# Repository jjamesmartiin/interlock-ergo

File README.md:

# Interlock Ergo

> **Disclaimer:** This project (firmware, PCB generation scripts, CAD models, and documentation) is an experimental keyboard design developed and maintained with AI assistance. Always verify schematics, board dimensions, gerber files, and dry-fit clearances before ordering physical fabrication or soldering components.

A wireless 68-key split ergonomic keyboard that **docks into one rigid keyboard**.
The two halves carry matching dovetail tabs and flush N52 magnets: lower one onto
the other and the joint closes, lift one and they separate. Both halves talk to a
USB dongle over low-power Bluetooth LE, so the host sees one ordinary USB HID
keyboard with no pairing and no drivers.

Two complete hardware variants are published, each with its own PCB and plate:

| | **Choc v1** | **Cherry MX** |
|---|---|---|
| Pitch | 18.0 × 17.0 mm | 19.05 × 19.05 mm |
| Plate | 1.2 mm | 1.5 mm |
| Case height | 14.2 mm | 16.0 mm |
| Case, docked | 350.2 × 137.6 mm | 367.5 × 147.8 mm |

---

## What makes it different

1. **It becomes one keyboard.** The left half carries two dovetail tabs on its
   seam face; the right half has the matching blind sockets. Four 6×3 mm N52
   magnets, flush with the seam faces, hold the joint closed. The undercut profile
   carries the load in tension and shear, so the seam behaves as one panel rather
   than two cases pushed together.
2. **A real USB keyboard, wirelessly.** A XIAO nRF52840 dongle is the ZMK split
   central and enumerates as a plain USB HID device. The halves reach it over
   Bluetooth LE at 2.4 GHz and bond with it once; the *host* never sees a
   Bluetooth device, so there is no pairing, no driver, and nothing to re-pair
   when you move between machines. It works in BIOS/UEFI and on laptops where
   Bluetooth is locked down by policy. Bluetooth profiles remain available
   (`&out OUT_BLE`) for phones and tablets.
3. **68 keys, all 1u.** No stabilisers, no wide keys, no non-standard keycap sizes
   to hunt for. ANSI row stagger (0 / 0.5 / 0.75 / 1.25 / 0.25 u) puts every letter
   column at the same offset it has on a GH60, so touch-typing transfers unchanged.
   There is no function column: 6 columns on the left and 8 on the right match a DZ60
   split down the middle (between 5 and 6), with a true inverted-T arrow cluster on
   the bottom right.
   The PCB, plate and case share one band stack, so the silhouette steps with the
   stagger and hugs the keys instead of being a rectangle with dead copper down one
   side of every row. The seam face stays a straight plane - it is the joint.

The diagram above is generated from the same constants the CAD and the PCB use
(`node docs/generate_layout.js`), so it cannot drift away from the hardware. Two
consequences of the straight seam that are worth knowing before you build:

- The row stagger needs 22.5 mm of horizontal shear. With a straight seam that
  shear ends up as dead case width on each half's seam edge, so the **centre gap
  between `5` and `6` is 69.1 mm (3.8 u)**, not the ~1.5 u of a normal staggered
  board. It is the same on every row. That is the price of a straight seam plane;
  a stepped seam would close it and is on the roadmap.
- `6`, `Y`, `H` and `N` all land on the right half (red column in the diagram),
  which is the usual convention for 6-column splits and matches ANSI.

---

## The parts

| | |
|---|---|
|  |  |
| Left half: seam face with the two dovetail tabs, USB-C window with its overmold relief, and the open controller bay | Right half: blind dovetail sockets and flush magnet pockets in the seam wall |
|  |  |
| Underside: four M2 bosses with the PCB mounts, cell recess in the controller bay | Plates: 14.0 mm switch apertures, stepped outline |
|  | |

Every STL in `cad/dist/` is gated by `tests/test_models.js`, which fails the
build if a part is more than one shell, is not watertight, or its dimensions
disagree with the stackup in `cad/interlock_params.scad`.

---

## Layout

```
[Esc  ] [1    ] [2    ] [3    ] [4    ] [5    ]  ‖ [6    ] [7    ] [8    ] [9    ] [0    ] [-    ] [=    ] [Bksp ]
   [Tab  ] [Q    ] [W    ] [E    ] [R    ] [T    ]  ‖ [Y    ] [U    ] [I    ] [O    ] [P    ] [[    ] []    ] [\    ]
     [Caps ] [A    ] [S    ] [D    ] [F    ] [G    ]  ‖ [H    ] [J    ] [K    ] [L    ] [;    ] ['    ] [Enter]
        [Shift] [Z    ] [X    ] [C    ] [V    ] [B    ]  ‖ [N    ] [M    ] [,    ] [.    ] [/    ] [Up   ] [Shift] [Del  ]
  [Ctrl ] [Win  ] [Alt  ] [Space] [Fn1  ]  ‖ [Space] [Alt  ] [Fn1  ] [Win  ] [Ctrl ] [Left ] [Down ] [Right]
```

Printed by `node docs/generate_layout.js` straight out of the keymap, with each
row indented by its ANSI stagger. 68 keys: 29 left + 39 right, in a 5 × 14 matrix.
`docs/kle_layout.json` is the same layout as a Keyboard-Layout-Editor file, and
`docs/matrix_and_pinout.md` has the electrical side. There is no function column
and no rotary encoder: both went when the layout was pulled back onto GH60's columns,
which is also why the left half is 29 keys and not 34.

---

## Repository

```
├── .github/workflows/build-zmk.yml   # firmware build + matrix tests + PCB DRC gate
├── cad/
│   ├── interlock_params.scad         # stackup, tolerances, joint and magnet geometry
│   ├── interlock_case.scad           # the case, shared by both switch standards
│   ├── interlock_case_{choc,mx}.scad # variant wrappers
│   ├── interlock_plate.scad          # switch plate, shared by both standards
│   ├── interlock_plate_{choc,mx}.scad
│   ├── dongle_case.scad              # XIAO BLE tray + friction-fit lid
│   ├── build_models.js               # headless STL build -> cad/dist/
│   ├── render_preview.js             # headless STL -> docs/images/*.png
│   └── dist/                         # printable STLs (generated, not committed)
├── config/boards/shields/interlock_ergo/
│   ├── Kconfig.shield, Kconfig.defconfig
│   ├── interlock_ergo.dtsi           # 68-key matrix transform
│   ├── interlock_ergo_{left,right,dongle}.overlay
│   ├── interlock_ergo_{left,right,dongle}.conf
│   └── interlock_ergo.keymap         # QWERTY, Nav/Fn, Media/BLE layers
├── docs/
│   ├── architecture.md               # design rationale and the dongle topology
│   ├── assembly.md                   # build order, torque, magnet polarity, flash steps
│   ├── bom.md                        # parts with vendor links
│   ├── matrix_and_pinout.md          # GPIO map and power tree
│   ├── part-dimensions.md            # every dimension the CAD rests on, with sources
│   ├── generate_layout.js            # draws docs/images/layout.svg from the real numbers
│   └── production-readiness-audit.md # adversarial review of the current tree
├── pcb/generate_pcb.js               # KiCad board generator + router + DRC gate
├── pcb/generate_schematic.js         # .kicad_sch from the verified board, with ERC
├── pcb/*.kicad_pcb                   # four boards: {left,right} x {choc,mx}
├── pcb/dist/                         # gerbers/BOM/CPL/schematic, only for DRC-clean boards
└── tests/
    ├── test_matrix.js                # firmware matrix, Kconfig, stagger agreement
    ├── test_models.js                # mesh watertightness + dimension gate
    ├── test_alignment.js             # PCB footprints vs plate apertures vs case rebate
    └── test_fab_rules.js             # process limits + order quantity per design
```

---

## Build and verify

```bash
node tests/test_matrix.js     # firmware matrix, shield config, CAD/PCB stagger agreement
node tests/test_models.js     # every STL is one watertight shell of the right size
node tests/test_alignment.js  # PCB footprints vs plate apertures vs case rebate, sampled in the meshes
node tests/test_fab_rules.js   # JLCPCB process limits and the order quantity per design
node cad/build_models.js      # rebuild all STLs
node cad/render_preview.js    # rebuild the README renders
node docs/generate_layout.js  # rebuild the layout diagram
node pcb/generate_pcb.js      # regenerate boards; DRC-clean boards emit fab files
node pcb/generate_schematic.js # regenerate the .kicad_sch files and their ERC/netlist gate
```

`pcb/generate_pcb.js` refuses to emit gerbers, BOM or CPL for any board that has
DRC violations or unconnected pads - **at any severity**, warnings included - and
withdraws previously published ones.
**If a gerber zip is missing from `pcb/dist/`, that board is not orderable** - fix
the routing, do not hand-build a zip from `pcb/*.kicad_pcb`.

Fabrication output is reproducible: KiCad's creation timestamps are pinned, so two
runs from the same sources produce byte-identical gerbers and a "gerbers changed"
diff always means the copper changed.

All of the above run in CI, including the DRC gate.

---

## Bill of materials

Full sourcing with vendor links: [docs/bom.md](docs/bom.md).

| Item | Qty | Notes |
|---|---|---|
| nice!nano v2 | 2 | one per half, castellated or socketed |
| Seeed XIAO nRF52840 (BLE) | 1 | USB dongle (central) |
| Kailh Choc v1 PG1350 **or** Cherry MX switches | 68 | pick one variant, not both |
| Kailh hotswap sockets | 68 | Choc `CPG135001S30` / MX `CPG151101S11`. The pin holes are unplated: **hotswap only**, switches cannot be soldered in directly |
| 1N4148W SOD-123 | 68 | one per key |
| MSK-12D19 slide switch | 2 | power, one per half |
| JST-PH 2.0 | 2 | cell connector |
| Protected LiPo pouch, LP402030 (4 × 20 × 30 mm cell) | 2 | ~200 mAh, **must** have a PCM — the PCM adds ~3.2 mm, so allow 34 mm overall |
| 6 × 3 mm N52 disc magnets | 4 | two per seam |
| M2 × 5 self-tapping screws | 8 | four per half |
| Plates | 1 pair | 3D printed, or 1.2 mm FR4 for Choc |

Battery reality check: the controller bay takes a 4.5 mm pack, and the documented
402030 is a **200 mAh** cell — not 250. With `CONFIG_ZMK_IDLE_SLEEP_TIMEOUT=900000`
that is roughly **1-2 weeks between charges**, not months. A bigger cell needs a
taller `standoff_h` in `cad/interlock_params.scad` and a re-print of both halves.

---

## Manufacturing

### PCBs

1. `node pcb/generate_pcb.js`. Only DRC-clean boards are written to `pcb/dist/`.
   `node pcb/generate_schematic.js` then emits the matching `.kicad_sch` and fails if
   its netlist disagrees with the board.
2. Order from JLCPCB: 2 layers, 1.6 mm, 1 oz copper, ENIG recommended for the
   hotswap pads, at the quantity in item 3 (5 pcs crosses the 650 cm² order-area
   threshold and adds a large-order surcharge).
3. **Quantity per design, not one number for everything.** The order-area budget is
   650 cm² and the boards are different sizes, so the right quantity differs:
   left Choc 3 pcs, right Choc 2, left MX 2, right MX 2. `node tests/test_fab_rules.js`
   prints the numbers for however you regenerate the boards - re-check them on the
   live JLCPCB quote, since the thresholds and fees change.
4. `bom_*.csv` / `cpl_*.csv` are only emitted for diodes, and the gerber zip
   carries the `B.Paste` stencil layer for them. Order them placed, or hand-solder
   them with everything else (sockets, headers, JST, slide switch) - hand-soldering
   is cheaper than JLCPCB's per-order PCBA fees at this volume.
5. Order both design variants only if you intend to build both; each half is a
   separate board because the halves are 29 and 39 keys and cannot be reversible.

### Printing

- PETG, 0.16 mm layers, 4 perimeters, 20% gyroid.
- Cases: print with the floor down. The seam tabs and the bay are vertical walls,
  so nothing needs support; only the two magnet pockets bridge, over 3.2 mm.
- Plates: 1.2 mm (Choc) / 1.5 mm (MX) exactly. Do not scale.
- Dongle: `dongle_case_base.stl` + `dongle_case_lid.stl`.
- Bed size: the left case is 160 × 138 mm, the right 193 × 138 mm (203 for MX), so a 220 × 220
  bed fits either half and a 256 × 256 bed fits both.

### Assembly

See [docs/assembly.md](docs/assembly.md). The order matters: solder the sockets
and diodes on the **bottom** of the PCB, screw the PCB to the four bosses, then
drop the plate in **last** - the switches hold the plate down.

---

## Firmware

CI builds all three shields. Download the artifact zip, then flash:

| Board | File |
|---|---|
| left half (nice!nano v2) | `interlock_ergo_left-nice_nano_v2-zmk.uf2` |
| right half (nice!nano v2) | `interlock_ergo_right-nice_nano_v2-zmk.uf2` |
| dongle (XIAO BLE) | `interlock_ergo_dongle-seeeduino_xiao_ble-zmk.uf2` |

CI also builds the dongle shield for `nice_nano_v2` and `nrf52840dongle_nrf52840`.
Those are firmware-only targets: the printed dongle case fits the XIAO, and the
Nordic USB-A dongle is a stick with no enclosure.

Double-tap reset to enter the UF2 bootloader and copy the file across. The dongle
bonds with both halves on first boot.

If the halves stop connecting after a reflash or a controller swap, flash
`settings_reset` on both halves and re-pair - it is built by the same workflow.

Local builds with Nix are available from `flake.nix`
(`nix build .#firmware-left`, `.#firmware-right`, `.#firmware-dongle`, `.#cad`, `.#pcb`,
or just `nix build` for the full release package).

All three shields are built and checked in CI. Two firmware details are pinned
rather than left to chance:

- `config/west.yml` pins ZMK **v0.2** (Zephyr 3.5).
- `flake.nix` pins the ARM compiler to **GCC 13**. nixpkgs' current
  `gcc-arm-embedded` is GCC 15, which rejects ZMK v0.2's `int` → `void *`
  `user_data` cast in `central_bas_proxy.c` as a hard error. Upstream only fixed
  that after v0.3.0 ([zmkfirmware/zmk#3105](https://github.com/zmkfirmware/zmk/pull/3105)).
  Move both pins together when you bump ZMK.

---

## Status

Every gate in this repository passes: the firmware matrix, the 3D-printed parts,
the plate/case/PCB alignment, the PCB DRC gate, and the fabrication-rule limits. All four boards route clean and
their JLCPCB gerber/BOM/CPL packages are in `pcb/dist/`.

What has *not* happened is a physical build. Nothing here has been printed,
soldered or typed on. Before ordering PCBs, print one half and dry-fit it - see
step 1 of [docs/assembly.md](docs/assembly.md).

Known limitations, in full: [docs/production-readiness-audit.md](docs/production-readiness-audit.md)
(69 mm docked centre gap, 200 mAh cell ceiling, no ESD/TVS protection).

Every mechanical dimension the CAD rests on, and where it came from:
[docs/part-dimensions.md](docs/part-dimensions.md).

## License

MIT. See [LICENSE](LICENSE).

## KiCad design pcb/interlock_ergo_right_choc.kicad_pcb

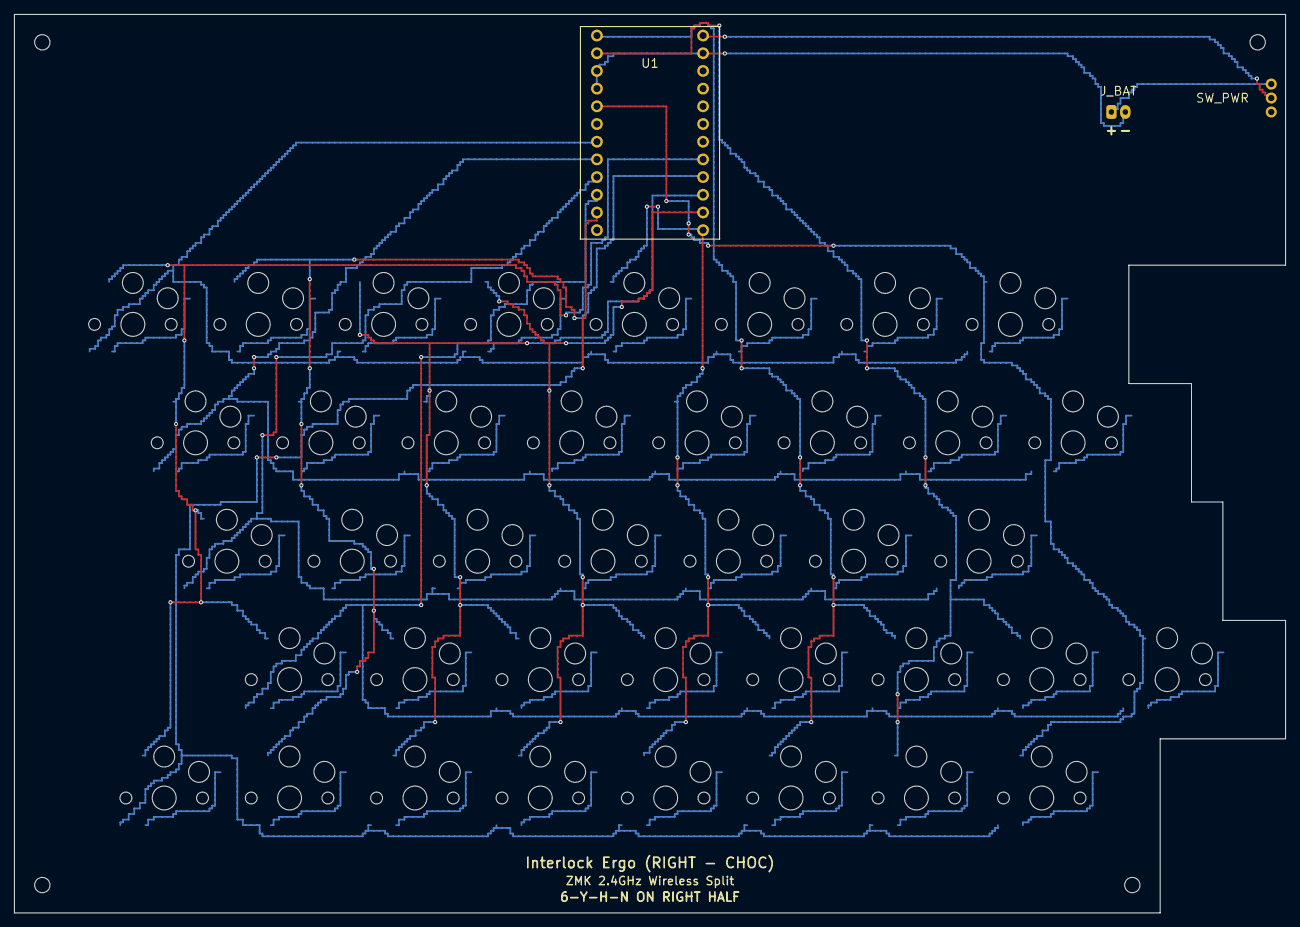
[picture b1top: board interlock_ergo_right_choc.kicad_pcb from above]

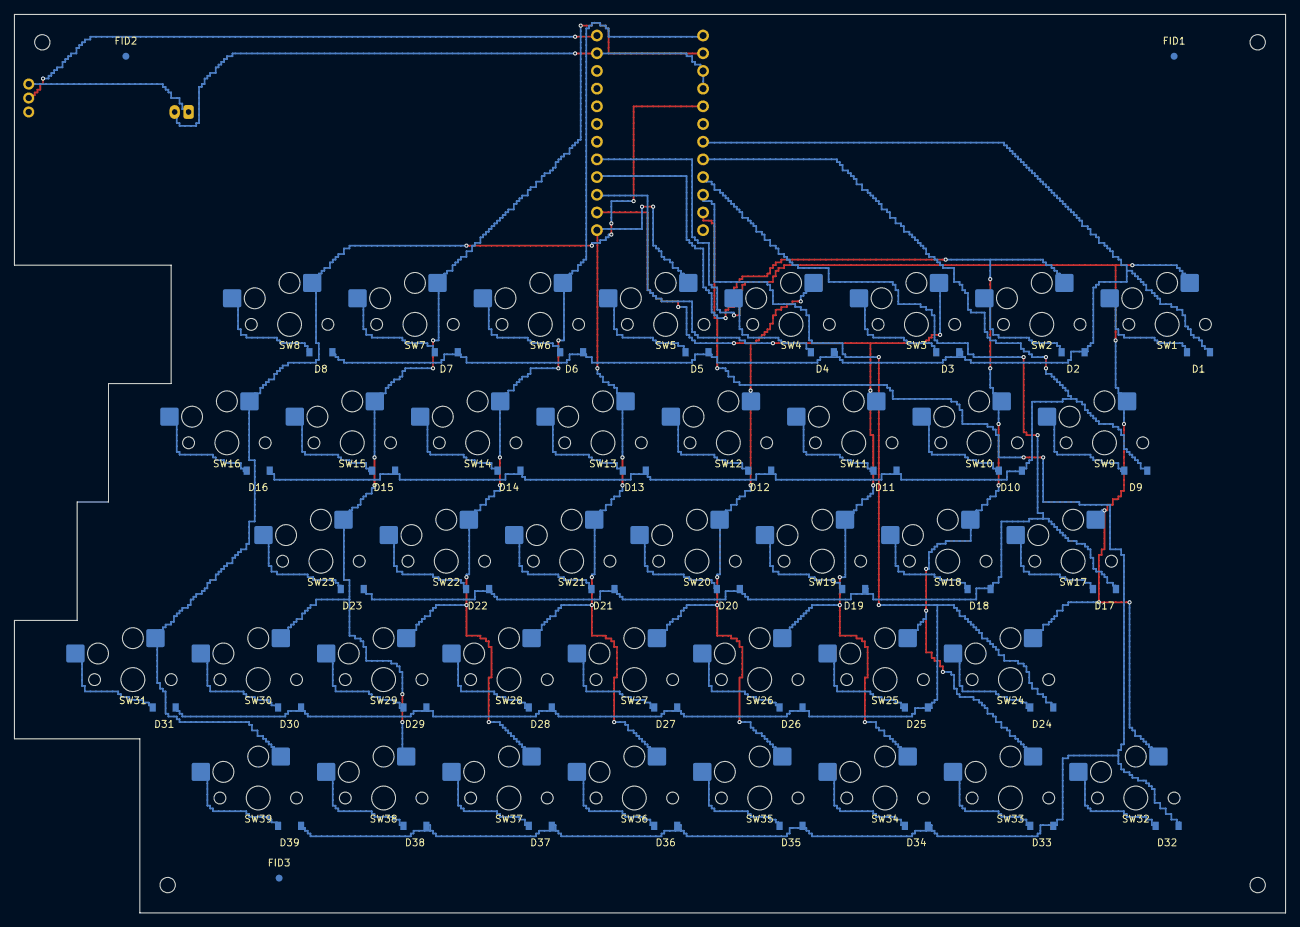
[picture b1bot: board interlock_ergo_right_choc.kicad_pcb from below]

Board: 2 copper layers, 182.5 x 129.0 mm, 84 parts (81 on the bottom side), 55 nets.

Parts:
D1, D2, D3, D4, D5, D6, D7, D8, D9, D10, D11, D12, D13, D14, D15, D16, D17, D18, D19, D20, D21, D22, D23, D24, D25, D26, D27, D28, D29, D30, D31, D32, D33, D34, D35, D36, D37, D38, D39: D_SOD-123
FID1, FID2, FID3: Fiducial_1mm_Mask2mm
J_BAT: JST_PH_S2B-PH-K_1x02
SW1, SW2, SW3, SW4, SW5, SW6, SW7, SW8, SW9, SW10, SW11, SW12, SW13, SW14, SW15, SW16, SW17, SW18, SW19, SW20, SW21, SW22, SW23, SW24, SW25, SW26, SW27, SW28, SW29, SW30, SW31, SW32, SW33, SW34, SW35, SW36, SW37, SW38, SW39: Kailh_Choc_V1_CPG135001S30
SW_PWR: SlideSwitch_MSK12D19
U1: NiceNano_v2_ProMicro

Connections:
BAT_PLUS: J_BAT.1, SW_PWR.1
COL6: SW1.1, SW9.1, SW17.1, SW24.1, SW32.1, U1.20
COL7: SW2.1, SW10.1, SW18.1, SW25.1, SW33.1, U1.21
COL8: SW3.1, SW11.1, SW19.1, SW26.1, SW34.1, U1.22
COL9: SW4.1, SW12.1, SW20.1, SW27.1, SW35.1, U1.23
COL10: SW5.1, SW13.1, SW21.1, SW28.1, SW36.1, U1.24
COL11: SW6.1, SW14.1, SW22.1, SW29.1, SW37.1, U1.1
COL12: SW7.1, SW15.1, SW23.1, SW30.1, SW38.1, U1.2
COL13: SW8.1, SW16.1, SW31.1, SW39.1, U1.5
GND: J_BAT.2, U1.3, U1.4, U1.14
RAW: SW_PWR.2, U1.13
ROW0: D1.1, D2.1, D3.1, D4.1, D5.1, D6.1, D7.1, D8.1, U1.7
ROW1: D9.1, D10.1, D11.1, D12.1, D13.1, D14.1, D15.1, D16.1, U1.8
ROW2: D17.1, D18.1, D19.1, D20.1, D21.1, D22.1, D23.1, U1.9
ROW3: D24.1, D25.1, D26.1, D27.1, D28.1, D29.1, D30.1, D31.1, U1.10
ROW4: D32.1, D33.1, D34.1, D35.1, D36.1, D37.1, D38.1, D39.1, U1.11
SW_D_R0_C0: D1.2, SW1.2
SW_D_R0_C1: D2.2, SW2.2
SW_D_R0_C2: D3.2, SW3.2
SW_D_R0_C3: D4.2, SW4.2
SW_D_R0_C4: D5.2, SW5.2
SW_D_R0_C5: D6.2, SW6.2
SW_D_R0_C6: D7.2, SW7.2
SW_D_R0_C7: D8.2, SW8.2
SW_D_R1_C0: D9.2, SW9.2
SW_D_R1_C1: D10.2, SW10.2
SW_D_R1_C2: D11.2, SW11.2
SW_D_R1_C3: D12.2, SW12.2
SW_D_R1_C4: D13.2, SW13.2
SW_D_R1_C5: D14.2, SW14.2
SW_D_R1_C6: D15.2, SW15.2
SW_D_R1_C7: D16.2, SW16.2
SW_D_R2_C0: D17.2, SW17.2
SW_D_R2_C1: D18.2, SW18.2
SW_D_R2_C2: D19.2, SW19.2
SW_D_R2_C3: D20.2, SW20.2
SW_D_R2_C4: D21.2, SW21.2
SW_D_R2_C5: D22.2, SW22.2
SW_D_R2_C6: D23.2, SW23.2
SW_D_R3_C0: D24.2, SW24.2
SW_D_R3_C1: D25.2, SW25.2
SW_D_R3_C2: D26.2, SW26.2
SW_D_R3_C3: D27.2, SW27.2
SW_D_R3_C4: D28.2, SW28.2
SW_D_R3_C5: D29.2, SW29.2
SW_D_R3_C6: D30.2, SW30.2
SW_D_R3_C7: D31.2, SW31.2
SW_D_R4_C0: D32.2, SW32.2
SW_D_R4_C1: D33.2, SW33.2
SW_D_R4_C2: D34.2, SW34.2
SW_D_R4_C3: D35.2, SW35.2
SW_D_R4_C4: D36.2, SW36.2
SW_D_R4_C5: D37.2, SW37.2
SW_D_R4_C6: D38.2, SW38.2
SW_D_R4_C7: D39.2, SW39.2

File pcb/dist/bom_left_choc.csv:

Comment,Designator,Footprint,LCSC Part #
Kailh Choc Hotswap Socket CPG135001S30,SW1,Kailh_Choc_V1_CPG135001S30,C5333465
1N4148W,D1,SOD-123,C81598
Kailh Choc Hotswap Socket CPG135001S30,SW2,Kailh_Choc_V1_CPG135001S30,C5333465
1N4148W,D2,SOD-123,C81598
Kailh Choc Hotswap Socket CPG135001S30,SW3,Kailh_Choc_V1_CPG135001S30,C5333465
1N4148W,D3,SOD-123,C81598
Kailh Choc Hotswap Socket CPG135001S30,SW4,Kailh_Choc_V1_CPG135001S30,C5333465
1N4148W,D4,SOD-123,C81598
Kailh Choc Hotswap Socket CPG135001S30,SW5,Kailh_Choc_V1_CPG135001S30,C5333465
1N4148W,D5,SOD-123,C81598
Kailh Choc Hotswap Socket CPG135001S30,SW6,Kailh_Choc_V1_CPG135001S30,C5333465
1N4148W,D6,SOD-123,C81598
Kailh Choc Hotswap Socket CPG135001S30,SW7,Kailh_Choc_V1_CPG135001S30,C5333465
1N4148W,D7,SOD-123,C81598
Kailh Choc Hotswap Socket CPG135001S30,SW8,Kailh_Choc_V1_CPG135001S30,C5333465
1N4148W,D8,SOD-123,C81598
Kailh Choc Hotswap Socket CPG135001S30,SW9,Kailh_Choc_V1_CPG135001S30,C5333465
1N4148W,D9,SOD-123,C81598
Kailh Choc Hotswap Socket CPG135001S30,SW10,Kailh_Choc_V1_CPG135001S30,C5333465
1N4148W,D10,SOD-123,C81598
Kailh Choc Hotswap Socket CPG135001S30,SW11,Kailh_Choc_V1_CPG135001S30,C5333465
1N4148W,D11,SOD-123,C81598
Kailh Choc Hotswap Socket CPG135001S30,SW12,Kailh_Choc_V1_CPG135001S30,C5333465
1N4148W,D12,SOD-123,C81598
Kailh Choc Hotswap Socket CPG135001S30,SW13,Kailh_Choc_V1_CPG135001S30,C5333465
1N4148W,D13,SOD-123,C81598
Kailh Choc Hotswap Socket CPG135001S30,SW14,Kailh_Choc_V1_CPG135001S30,C5333465
1N4148W,D14,SOD-123,C81598
Kailh Choc Hotswap Socket CPG135001S30,SW15,Kailh_Choc_V1_CPG135001S30,C5333465
1N4148W,D15,SOD-123,C81598
Kailh Choc Hotswap Socket CPG135001S30,SW16,Kailh_Choc_V1_CPG135001S30,C5333465
1N4148W,D16,SOD-123,C81598
Kailh Choc Hotswap Socket CPG135001S30,SW17,Kailh_Choc_V1_CPG135001S30,C5333465
1N4148W,D17,SOD-123,C81598
Kailh Choc Hotswap Socket CPG135001S30,SW18,Kailh_Choc_V1_CPG135001S30,C5333465
1N4148W,D18,SOD-123,C81598
Kailh Choc Hotswap Socket CPG135001S30,SW19,Kailh_Choc_V1_CPG135001S30,C5333465
1N4148W,D19,SOD-123,C81598
Kailh Choc Hotswap Socket CPG135001S30,SW20,Kailh_Choc_V1_CPG135001S30,C5333465
1N4148W,D20,SOD-123,C81598
Kailh Choc Hotswap Socket CPG135001S30,SW21,Kailh_Choc_V1_CPG135001S30,C5333465
1N4148W,D21,SOD-123,C81598
Kailh Choc Hotswap Socket CPG135001S30,SW22,Kailh_Choc_V1_CPG135001S30,C5333465
1N4148W,D22,SOD-123,C81598
Kailh Choc Hotswap Socket CPG135001S30,SW23,Kailh_Choc_V1_CPG135001S30,C5333465
1N4148W,D23,SOD-123,C81598
Kailh Choc Hotswap Socket CPG135001S30,SW24,Kailh_Choc_V1_CPG135001S30,C5333465
1N4148W,D24,SOD-123,C81598
Kailh Choc Hotswap Socket CPG135001S30,SW25,Kailh_Choc_V1_CPG135001S30,C5333465
1N4148W,D25,SOD-123,C81598
Kailh Choc Hotswap Socket CPG135001S30,SW26,Kailh_Choc_V1_CPG135001S30,C5333465
1N4148W,D26,SOD-123,C81598
Kailh Choc Hotswap Socket CPG135001S30,SW27,Kailh_Choc_V1_CPG135001S30,C5333465
1N4148W,D27,SOD-123,C81598
Kailh Choc Hotswap Socket CPG135001S30,SW28,Kailh_Choc_V1_CPG135001S30,C5333465
1N4148W,D28,SOD-123,C81598
Kailh Choc Hotswap Socket CPG135001S30,SW29,Kailh_Choc_V1_CPG135001S30,C5333465
1N4148W,D29,SOD-123,C81598
